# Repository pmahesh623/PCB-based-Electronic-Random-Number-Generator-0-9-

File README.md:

# PCB-based-Electronic-Random-Number-Generator-0-9-
## Project Overview
This project is a PCB-based electronic random number generator developed using the **NE555 Timer IC, CD4026 Decade Counter IC, Common Cathode 7-Segment Display, and a Push-Button Switch**. The circuit generates and displays numerical outputs electronically, demonstrating the practical application of timer circuits, digital counters, and display interfacing.

The NE555 timer is configured to generate clock pulses, which are processed by the CD4026 decade counter to drive the 7-segment display. The push-button switch provides user interaction, allowing the circuit to operate as a compact electronic number generator.

## Components Used
- NE555 Timer IC
- CD4026 Decade Counter IC
- Common Cathode 7-Segment Display
- Push-Button Switch
- Resistors and Capacitors
- Printed Circuit Board (PCB)
- Power Supply and Connecting Components

## Working Principle
1. **Clock Pulse Generation:** The NE555 timer generates continuous clock pulses.
2. **Digital Counting:** The CD4026 counts the incoming pulses and produces the appropriate outputs for numerical display.
3. **Number Display:** The common cathode 7-segment display shows the corresponding digit.
4. **User Interaction:** The push-button switch provides manual control of the circuit, depending on the implemented switching arrangement.

## Key Features
- Compact PCB-based design
- Simple and cost-effective electronic circuit
- Real-time digital number display
- Low-component-count implementation
- Practical demonstration of timer and counter ICs
- Suitable for electronics laboratory experiments and educational projects

## Applications
- Digital electronics learning and demonstrations
- Basic random-number generation experiments
- Counter and display interfacing projects
- Educational PCB design and prototyping

## Learning Outcomes
This project provides hands-on experience in PCB design, soldering, timer circuit configuration, digital counter operation, and 7-segment display interfacing.

## Technologies and Concepts
- Analog and Digital Electronics
- NE555 Timer Circuit
- CD4026 Decade Counter
- Common Cathode 7-Segment Display
- PCB Design and Hardware Prototyping

## Future Improvements
- Add adjustable counting speed
- Improve button-based control and reset functionality
- Develop a more compact PCB layout
- Explore alternative digital number-generation techniques

**Project Type:** Electronics Hardware Project  
**Core Components:** NE555, CD4026, 7-Segment Display  
**Platform:** Custom PCB

*Note: This circuit produces a cycling numerical sequence rather than inherently random numbers. Its randomness depends on the implemented control and sampling mechanism.*

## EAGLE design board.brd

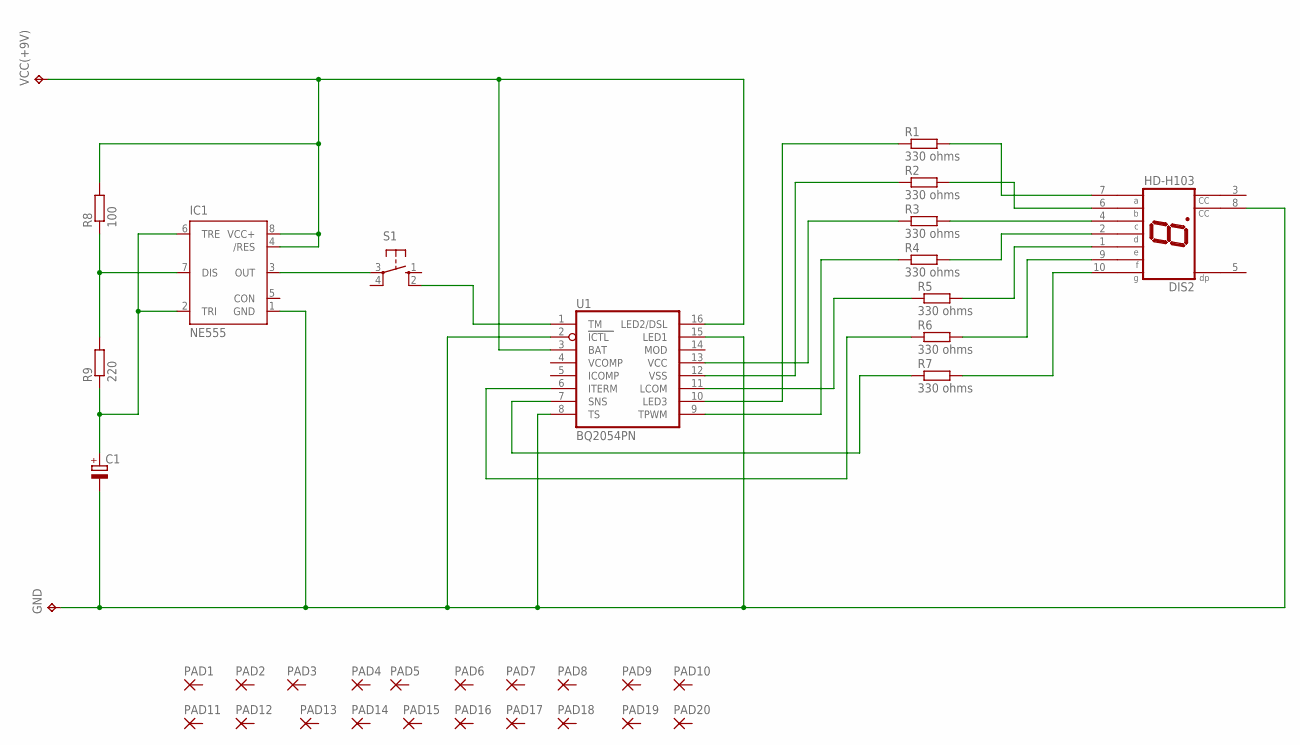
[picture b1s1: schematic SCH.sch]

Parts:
C1: CPOL-EUB45181B; B45181B
DIS2: HD-H103; HDSP-M
GND: TPPAD1-13Y; P1-13Y
IC1: NE555; DIL-08
PAD1, PAD2, PAD3, PAD4, PAD5, PAD6, PAD7, PAD8, PAD9, PAD10, PAD11, PAD12, PAD13, PAD14, PAD15, PAD16, PAD17, PAD18, PAD19, PAD20: 2,54/0,8
R1, R2, R3, R4, R5, R6, R7: 330 ohms; 0207/10
R8: 100; 0207/10
R9: 220; 0207/10
S1: 40-XX; B3F-40XX
U1: BQ2054PN; DIL16
VCC(+9V): TPPAD1-13Y; P1-13Y

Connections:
unnamed: R1.1, U1.10 (LED3)
unnamed: R2.1, U1.12 (VSS)
unnamed: R3.1, U1.13 (VCC)
unnamed: R4.1, U1.9 (TPWM)
unnamed: R5.1, U1.11 (LCOM)
unnamed: R6.1, U1.6 (ITERM)
unnamed: R7.1, U1.7 (SNS)
unnamed: DIS2.7 (A), R1.2
unnamed: DIS2.6 (B), R2.2
unnamed: DIS2.4 (C), R3.2
unnamed: DIS2.2 (D), R4.2
unnamed: DIS2.1 (E), R5.2
unnamed: DIS2.9 (F), R6.2
unnamed: DIS2.10 (G), R7.2
unnamed: C1.-, DIS2.8 (CC), GND.TP, IC1.1 (GND), U1.2 (ICTL), U1.8 (TS), U1.15 (LED1)
unnamed: IC1.4 (/RES), IC1.8 (VCC+), R8.2, U1.3 (BAT), U1.16 (LED2/DSL), VCC(+9V).TP
unnamed: IC1.7 (DIS), R8.1, R9.2
unnamed: C1.+, IC1.2 (TRI), IC1.6 (TRE), R9.1
unnamed: IC1.3 (OUT), S1.3
unnamed: S1.2 (S1), U1.1 (TM)

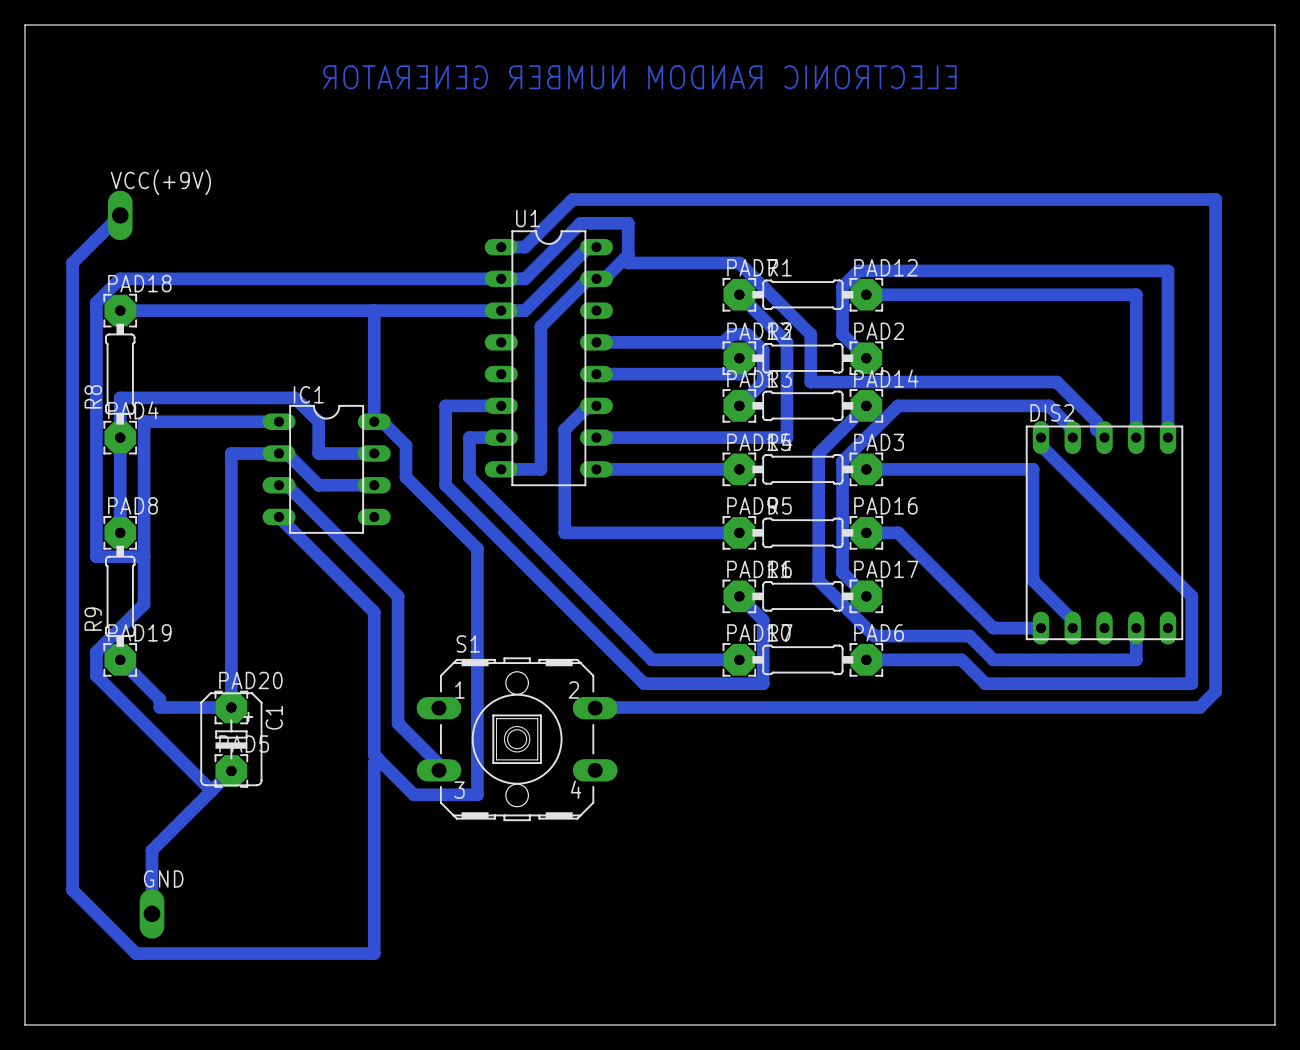
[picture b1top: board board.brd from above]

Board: 2 copper layers, 100.0 x 80.0 mm, 36 parts (0 on the bottom side), 20 nets.
